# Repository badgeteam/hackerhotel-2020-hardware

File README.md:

# Hackerhotel 2020 badge
We hope you enjoyed the event!

# Using the design
Should you want to use this design for your own badges then keep in mind that the LED footprints are reversed. Because of this the current design is only suitable for manual assembly! Should you find time to create a version with the LED footprints the right way round (or with the transistors moved to the other side of the LEDs...) then please let us know by creating a pull request.

# License
CERN-OHL-P

Please send in an issue to this repository if you want to use this work under a different license.

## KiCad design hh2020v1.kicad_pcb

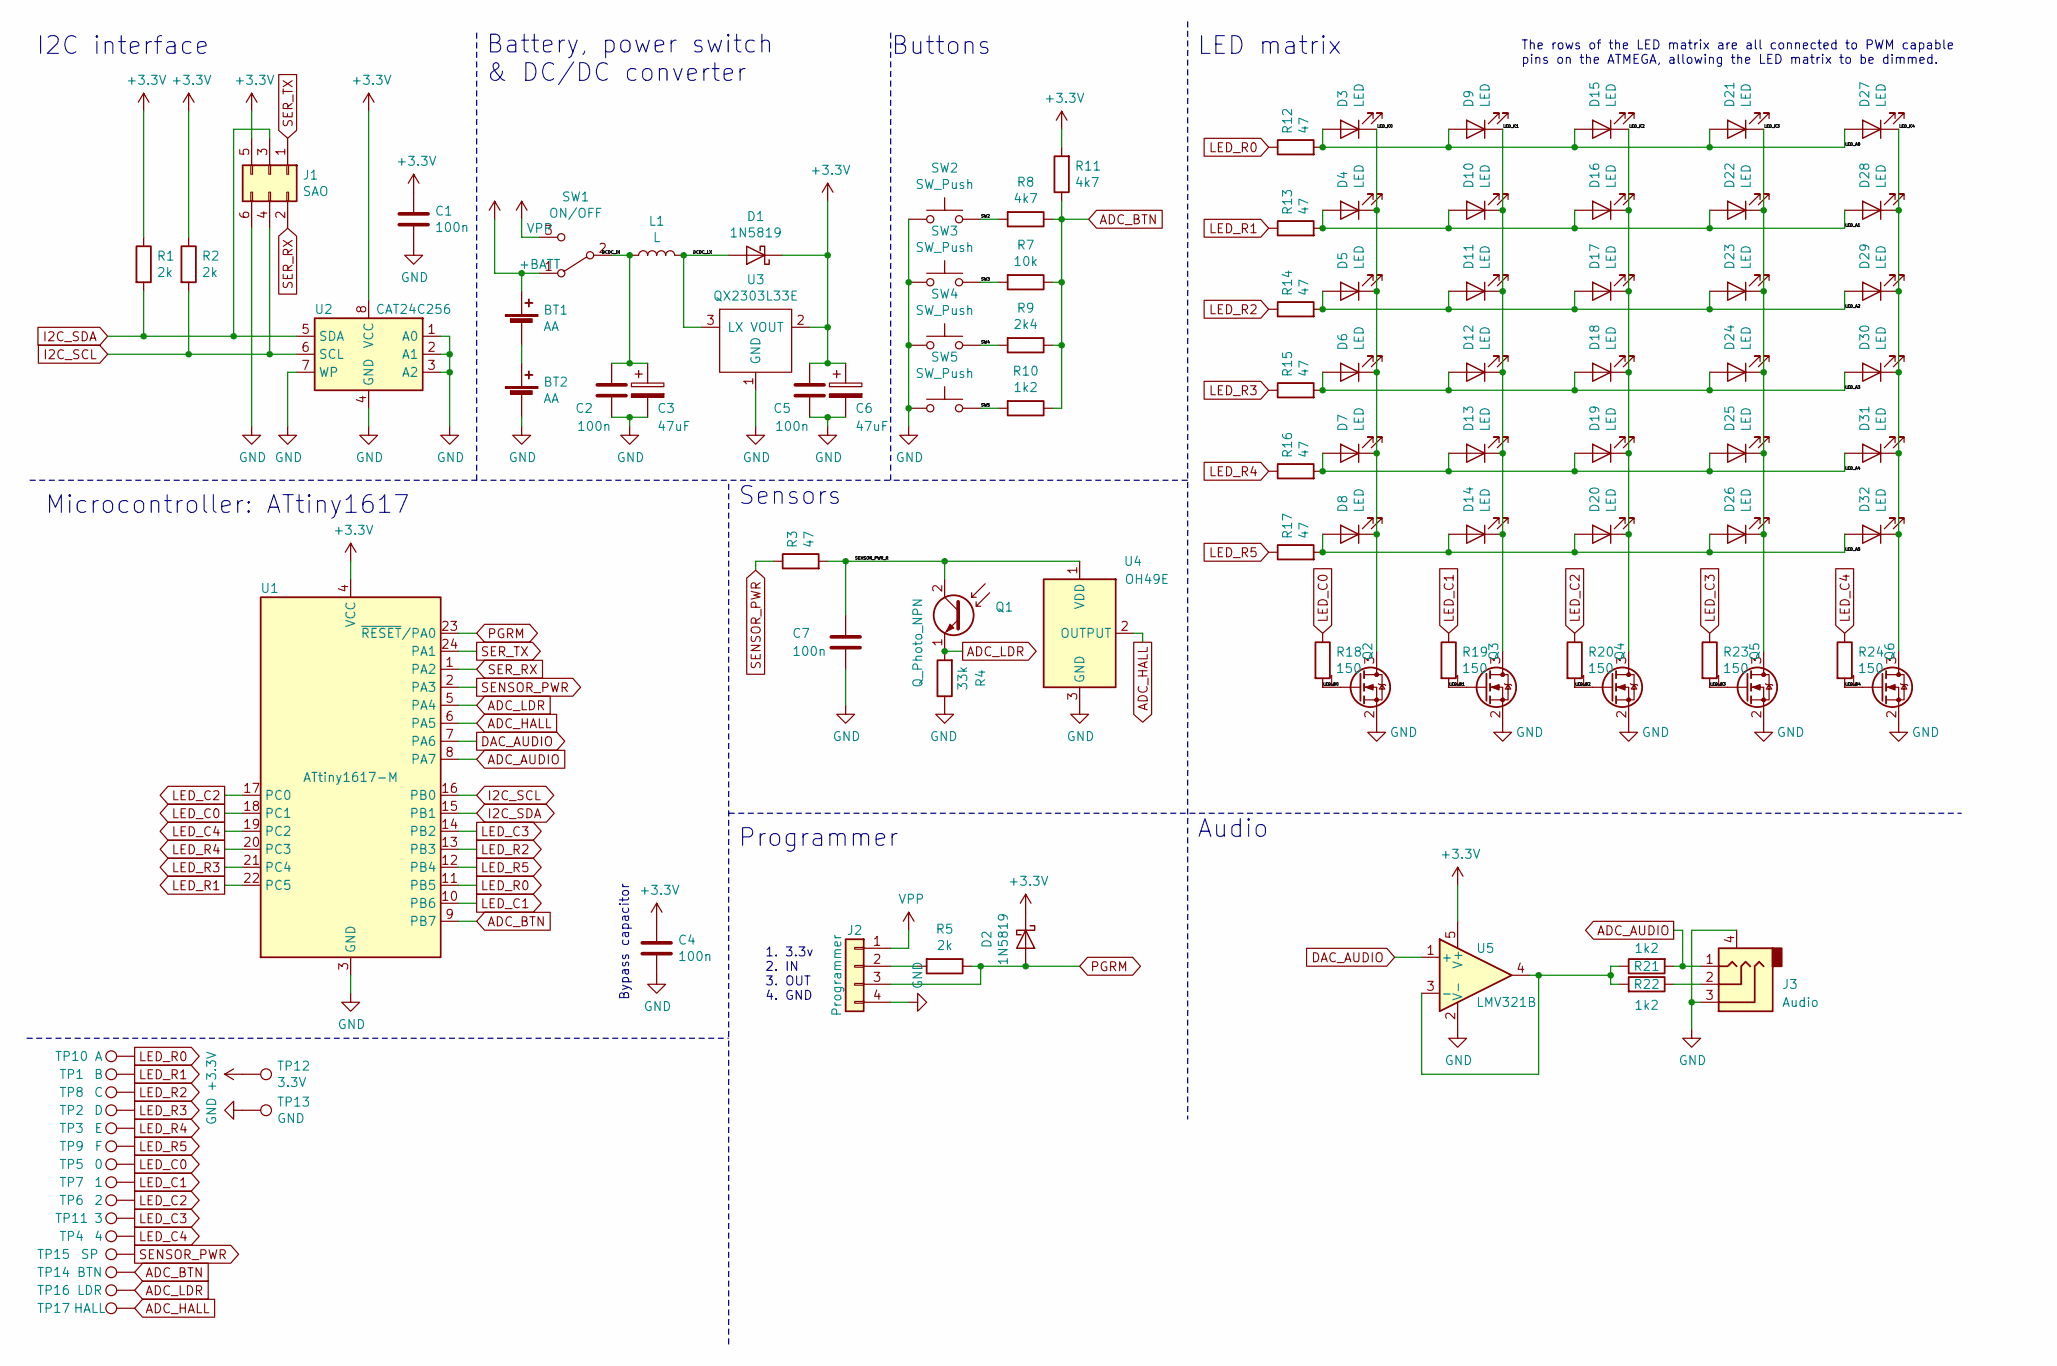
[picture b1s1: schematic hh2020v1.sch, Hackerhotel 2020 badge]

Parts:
BT1, BT2: AA; BatteryHolder_Keystone_2460_1xAA
C1, C2, C4, C5, C7: 100n; C_0603
C3, C6: 47uF; CP_Tantalum_Case-A_EIA-3216-18_Reflow
D1, D2: 1N5819; D_SOD-123
D3, D4, D5, D6, D7, D8, D9, D10, D11, D12, D13, D14, D15, D16, D17, D18, D19, D20, D21, D22, D23, D24, D25, D26, D27, D28, D29, D30, D31, D32: LED; led-sideways-2.0x0.5
J1: SAO; Pin_Header_Straight_2x03_Pitch2.54mm
J2: Programmer; Pin_Header_Straight_1x04_Pitch2.54mm
J3: Audio; PJ320D_3.5mm_Jack
L1: L; L_Bourns-SRN8040_8x8.15mm
Q1: Q_Photo_NPN; R_0805
Q2, Q3, Q4, Q5, Q6: Q_NMOS_GSD; SOT-23
R1, R2, R5: 2k; R_0603
R3, R12, R13, R14, R15, R16, R17: 47; R_0603
R4: 33k; R_0603
R7: 10k; R_0603
R8, R11: 4k7; R_0603
R9: 2k4; R_0603
R10, R21, R22: 1k2; R_0603
R18, R19, R20, R23, R24: 150; R_0603
SW1: ON/OFF; SW_SPDT_PCM12
SW2, SW3, SW4, SW5: SW_Push; SW_SPST_SKQG
TP1: B; TestPoint_Pad_1.0x1.0mm
TP2: D; TestPoint_Pad_1.0x1.0mm
TP3: E; TestPoint_Pad_1.0x1.0mm
TP4: 4; TestPoint_Pad_1.0x1.0mm
TP5: 0; TestPoint_Pad_1.0x1.0mm
TP6: 2; TestPoint_Pad_1.0x1.0mm
TP7: 1; TestPoint_Pad_1.0x1.0mm
TP8: C; TestPoint_Pad_1.0x1.0mm
TP9: F; TestPoint_Pad_1.0x1.0mm
TP10: A; TestPoint_Pad_1.0x1.0mm
TP11: 3; TestPoint_Pad_1.0x1.0mm
TP12: 3.3V; TestPoint_Pad_1.0x1.0mm
TP13: GND; TestPoint_Pad_1.0x1.0mm
TP14: BTN; TestPoint_Pad_1.0x1.0mm
TP15: SP; TestPoint_Pad_1.0x1.0mm
TP16: LDR; TestPoint_Pad_1.0x1.0mm
TP17: HALL; TestPoint_Pad_1.0x1.0mm
U1: ATtiny1617-M; QFN-24-1EP_4x4mm_P0.5mm_EP2.6x2.6mm
U2: CAT24C256; SOIC-8-N
U3: QX2303L33E; SOT-89-3
U4: OH49E; SOT-23
U5: LMV321B; SOT-23-5

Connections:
+3V3: C1.1, C4.1, C5.2, C6.1, D1.1 (K), D2.1 (K), J1.5, R1.1, R2.1, R11.2, TP12.1, U1.4 (VCC), U2.8 (VCC), U3.2 (VOUT), U5.5 (V+)
+BATT: BT1.1 (+), SW1.1 (A)
/DCDC_IN: C2.2, C3.1, L1.1, SW1.2 (B)
/DCDC_LX: D1.2 (A), L1.2, U3.3 (LX)
/LED_A0: D3.2 (A), D9.2 (A), D15.2 (A), D21.2 (A), D27.2 (A), R12.2
/LED_A1: D4.2 (A), D10.2 (A), D16.2 (A), D22.2 (A), D28.2 (A), R13.2
/LED_A2: D5.2 (A), D11.2 (A), D17.2 (A), D23.2 (A), D29.2 (A), R14.2
/LED_A3: D6.2 (A), D12.2 (A), D18.2 (A), D24.2 (A), D30.2 (A), R15.2
/LED_A4: D7.2 (A), D13.2 (A), D19.2 (A), D25.2 (A), D31.2 (A), R16.2
/LED_A5: D8.2 (A), D14.2 (A), D20.2 (A), D26.2 (A), D32.2 (A), R17.2
/LED_B0: Q2.1 (G), R18.2
/LED_B1: Q3.1 (G), R19.2
/LED_B2: Q4.1 (G), R20.2
/LED_B3: Q5.1 (G), R23.2
/LED_B4: Q6.1 (G), R24.2
/LED_K0: D3.1 (K), D4.1 (K), D5.1 (K), D6.1 (K), D7.1 (K), D8.1 (K), Q2.3 (D)
/LED_K1: D9.1 (K), D10.1 (K), D11.1 (K), D12.1 (K), D13.1 (K), D14.1 (K), Q3.3 (D)
/LED_K2: D15.1 (K), D16.1 (K), D17.1 (K), D18.1 (K), D19.1 (K), D20.1 (K), Q4.3 (D)
/LED_K3: D21.1 (K), D22.1 (K), D23.1 (K), D24.1 (K), D25.1 (K), D26.1 (K), Q5.3 (D)
/LED_K4: D27.1 (K), D28.1 (K), D29.1 (K), D30.1 (K), D31.1 (K), D32.1 (K), Q6.3 (D)
/SENSOR_PWR_R: C7.1, Q1.2 (E), R3.2, U4.1 (VDD)
/SW2: R8.2, SW2.2
/SW3: R7.2, SW3.2
/SW4: R9.2, SW4.2
/SW5: R10.2, SW5.2
ADC_AUDIO: J3.1, R21.2, U1.8 (PA7)
ADC_BTN: R7.1, R8.1, R9.1, R10.1, R11.1, TP14.1, U1.9 (PB7)
ADC_HALL: TP17.1, U1.6 (PA5), U4.2 (OUTPUT)
ADC_LDR: Q1.1 (C), R4.2, TP16.1, U1.5 (PA4)
DAC_AUDIO: U1.7 (PA6), U5.1 (+)
GND: BT2.2 (-), C1.2, C2.1, C3.2, C4.2, C5.1, C6.2, C7.2, J1.6, J2.4, J3.3, J3.4, Q2.2 (S), Q3.2 (S), Q4.2 (S), Q5.2 (S), Q6.2 (S), R4.1, SW2.1, SW3.1, SW4.1, SW5.1, TP13.1, U1.3 (GND), U1.25 (GND), U2.1 (A0), U2.2 (A1), U2.3 (A2), U2.4 (GND), U2.7 (WP), U3.1 (GND), U4.3 (GND), U5.2 (V-)
I2C_SCL: J1.4, R2.2, U1.16 (PB0), U2.6 (SCL)
I2C_SDA: J1.3, R1.2, U1.15 (PB1), U2.5 (SDA)
LED_C0: R18.1, TP5.1, U1.18 (PC1)
LED_C1: R19.1, TP7.1, U1.10 (PB6)
LED_C2: R20.1, TP6.1, U1.17 (PC0)
LED_C3: R23.1, TP11.1, U1.14 (PB2)
LED_C4: R24.1, TP4.1, U1.19 (PC2)
LED_R0: R12.1, TP10.1, U1.11 (PB5)
LED_R1: R13.1, TP1.1, U1.22 (PC5)
LED_R2: R14.1, TP8.1, U1.13 (PB3)
LED_R3: R15.1, TP2.1, U1.21 (PC4)
LED_R4: R16.1, TP3.1, U1.20 (PC3)
LED_R5: R17.1, TP9.1, U1.12 (PB4)
unnamed: BT1.2 (-), BT2.1 (+)
unnamed: J2.2, R5.2
unnamed: J3.2, R22.1
unnamed: R21.1, R22.2, U5.3 (-), U5.4
PGRM: D2.2 (A), J2.3, R5.1, U1.23 (~RESET~/PA0)
SENSOR_PWR: R3.1, TP15.1, U1.2 (PA3)
SER_RX: J1.2, U1.1 (PA2)
SER_TX: J1.1, U1.24 (PA1)
VPP: J2.1, SW1.3 (C)

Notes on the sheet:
LED matrix
Buttons
Microcontroller: ATtiny1617
I2C interface
Bypass capacitor
Battery, power switch & DC/DC converter
Audio
Sensors
The rows of the LED matrix are all connected to PWM capable pins on the ATMEGA, allowing the LED matrix to be dimmed.
1. 3.3v 2. IN 3. OUT 4. GND
Programmer

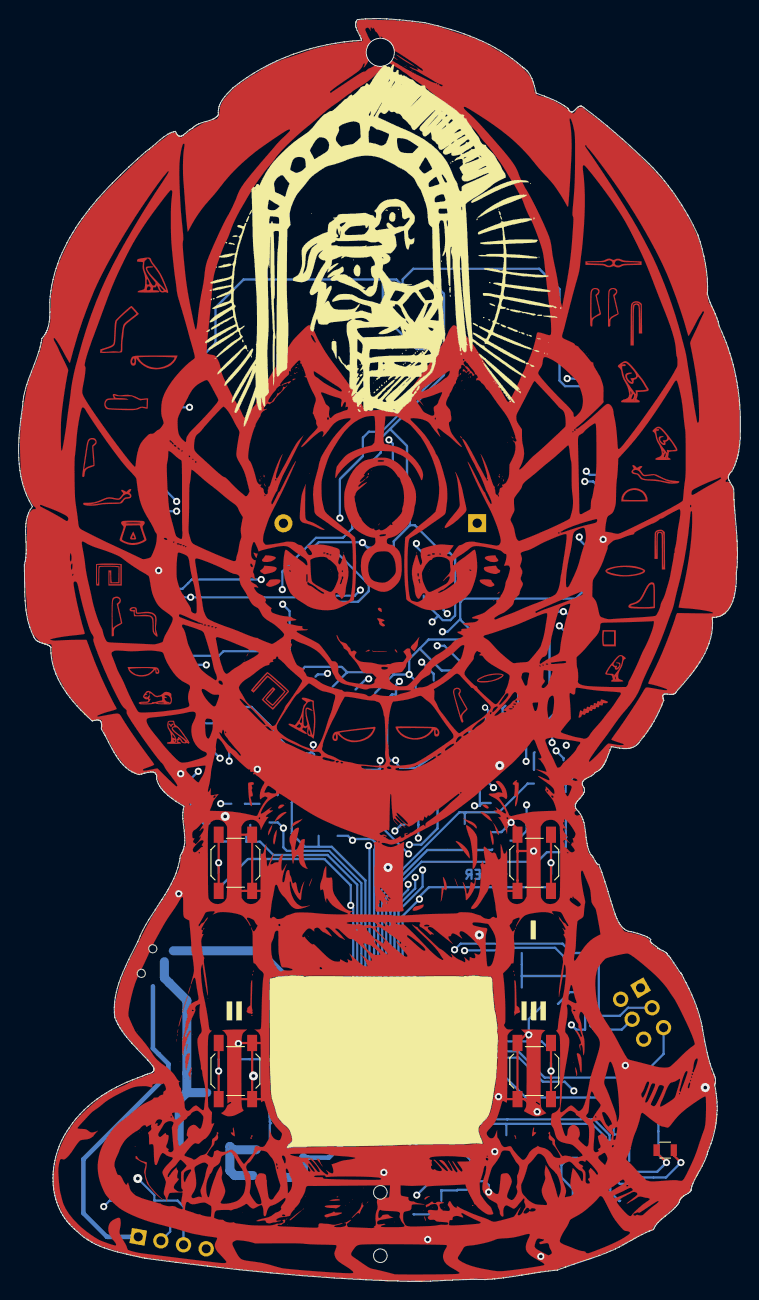
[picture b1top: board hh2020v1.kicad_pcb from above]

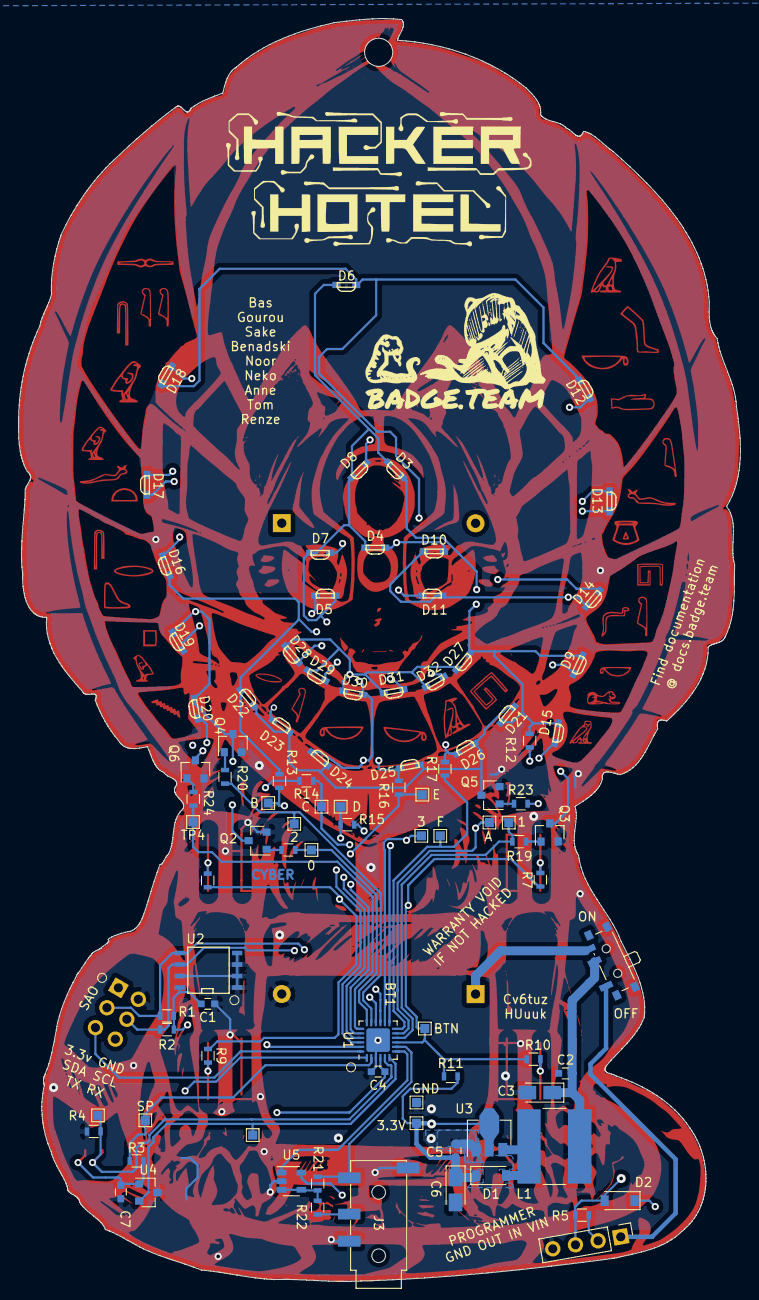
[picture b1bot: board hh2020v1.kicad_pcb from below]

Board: 4 copper layers, 79.7 x 139.5 mm, 104 parts (95 on the bottom side), 53 nets.

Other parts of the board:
Ref**: Val**; catshape4
Ref**#2: Val**; hackerhotel
Ref**#3: Val**; badgeteam

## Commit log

2020-02-16 Enjoy!
2020-07-05 Add licence text

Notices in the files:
hh2020v1.sch:
License: Cern OSHW
